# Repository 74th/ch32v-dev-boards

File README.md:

# CH32V Development Board

- [74th. CH32V203C8T6 ProMicro](./ch32v203-promicro/)
- [74th. CH32V003F6P6 ProMicro](./ch32v003-promicro/)
- [74th. CH32X035G8U6 ProMicro for USB PD](./ch32x035-promicro-usb-pd/)
- [74th. CH32X035G8U6 ProMicro for USB Device](./ch32x035-promicro-usb-device/)
- [74th. CH32V00xJxM6 SOIC-8 Dev Board](./ch32v00x-soic8/)
- [74th. CH32V006K8U6 Full Dev Board](./ch32v006-full/)

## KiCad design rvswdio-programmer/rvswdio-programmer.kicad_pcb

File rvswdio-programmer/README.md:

# RVSWDIO Programmer

- Semantics [kicanvas](https://kicanvas.org/?github=https%3A%2F%2Fgithub.com%2F74th%2Fch32v-dev-boards%2Fblob%2Frvswdio-programmer%2F1.0.1%2Frvswdio-programmer%2Frvswdio-programmer.kicad_sch)
- PCB [kicanvas](https://kicanvas.org/?github=https%3A%2F%2Fgithub.com%2F74th%2Fch32v-dev-boards%2Fblob%2Frvswdio-programmer%2F1.0.1%2Frvswdio-programmer%2Frvswdio-programmer.kicad_pcb)

firmware

https://github.com/cnlohr/rv003usb/tree/master/rvswdio_programmer

The on/off levels of the power switch pin need to be swapped.

```h
#define POWER_ON 0
#define POWER_OFF 1
```

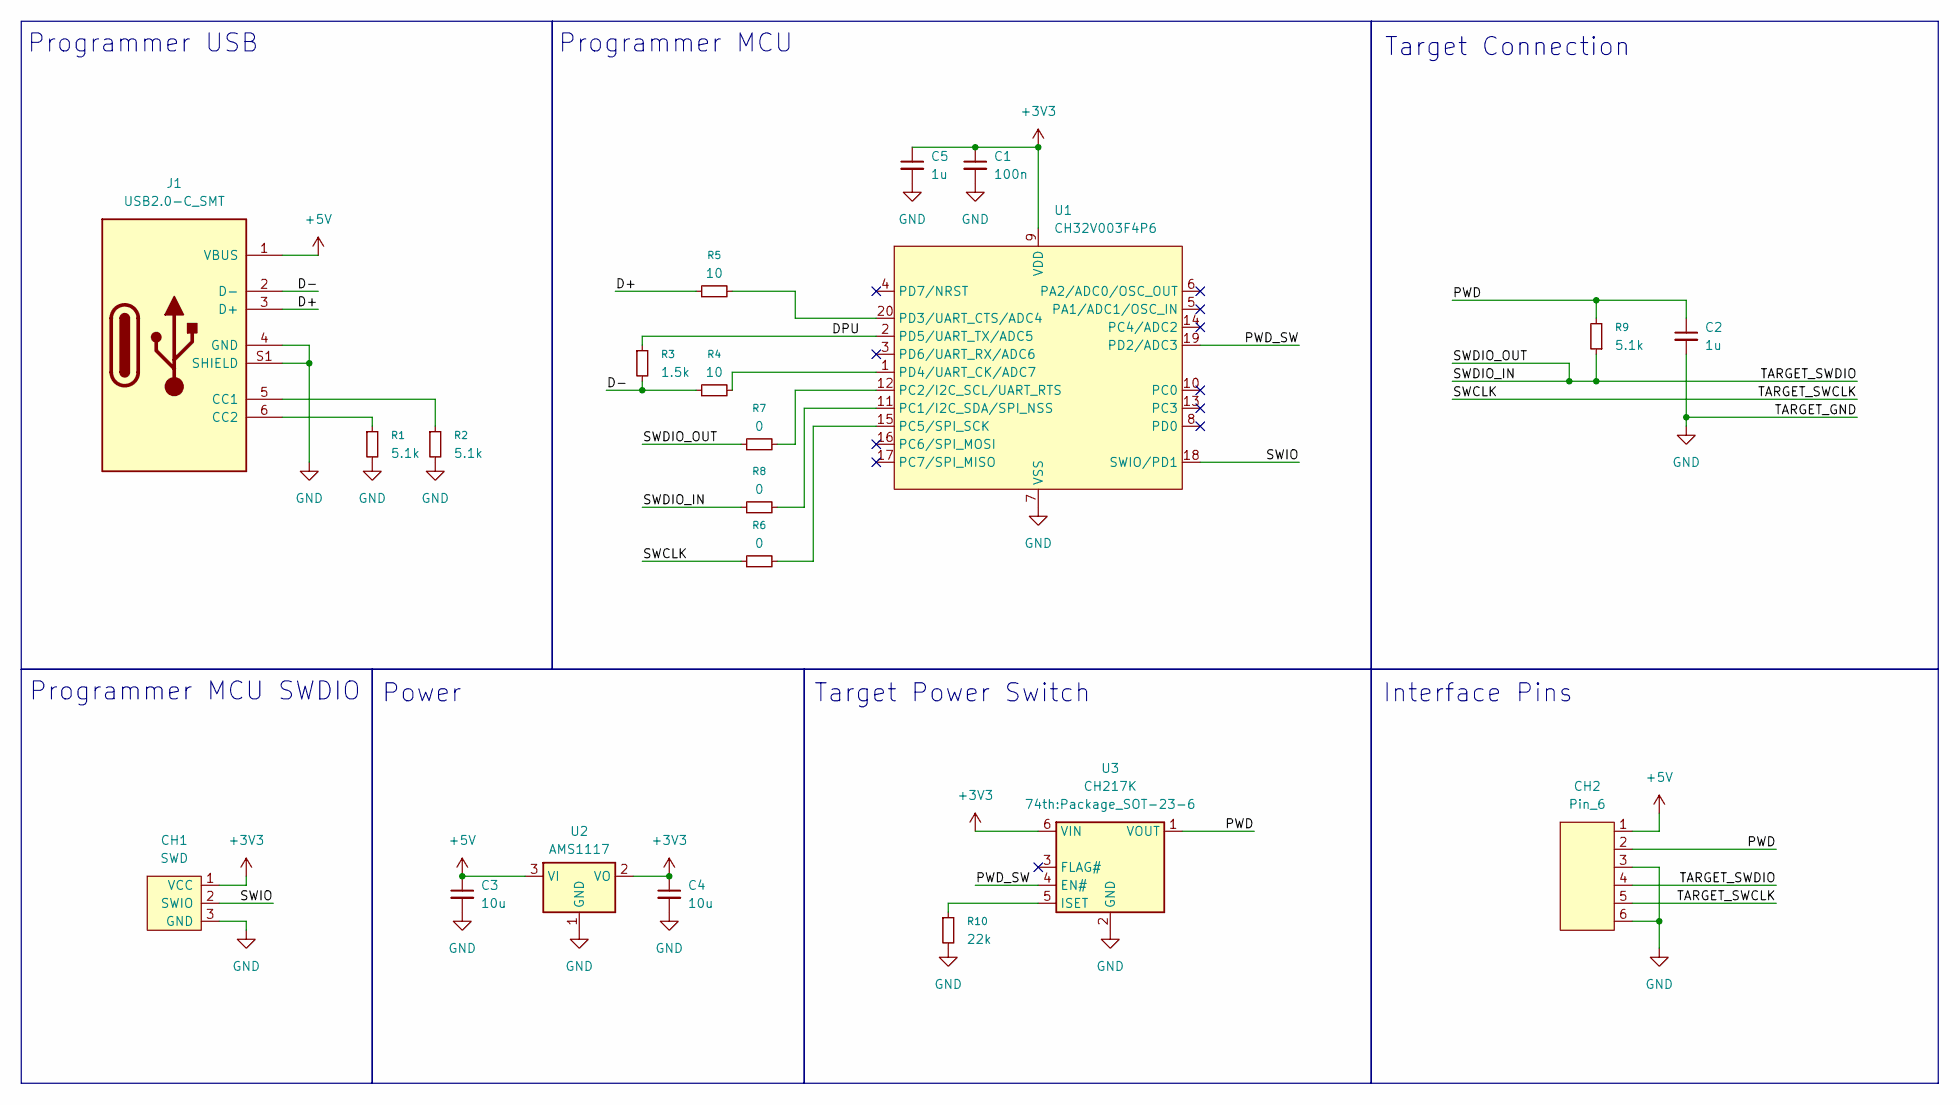
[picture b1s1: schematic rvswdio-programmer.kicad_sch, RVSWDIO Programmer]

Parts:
C1: 100n; Capacitor_0603_1608
C2, C5: 1u; Capacitor_0603_1608
C3, C4: 10u; Capacitor_0603_1608
CH1: SWD; PinOut_Pin_3_3GND
CH2: Pin_6; PinOut_Pin_6_GND
J1: USB2.0-C_SMT; Connector_USB-C-Receptacle_SMT_12-Pin_Simple
R1, R2, R9: 5.1k; Register_0603_1608
R3: 1.5k; Register_0603_1608
R4, R5: 10; Register_0603_1608
R6, R7, R8: 0; Register_0603_1608
R10: 22k; Register_0603_1608
U1: CH32V003F4P6; Package_TSSOP-20_4.4x6.5mm_P0.65mm
U2: AMS1117; Package_SOT-89-3
U3: CH217K; Package_SOT-23-6

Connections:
+3V3: C1.1, C4.1, C5.1, CH1.1 (VCC), U1.9 (VDD), U2.2 (VO), U3.6 (VIN)
+5V: C3.1, CH2.1, J1.1 (VBUS), U2.3 (VI)
/D+: J1.3 (D+), R5.1
/D-: J1.2 (D-), R3.2, R4.1
/DPU: R3.1, U1.2 (PD5/UART_TX/ADC5)
/PWD: C2.1, CH2.2, R9.2, U3.1 (VOUT)
/PWD_SW: U1.19 (PD2/ADC3), U3.4 (EN#)
/SWCLK: CH2.5, R6.1
/SWDIO_IN: CH2.4, R7.1, R8.1, R9.1
/SWIO: CH1.2 (SWIO), U1.18 (SWIO/PD1)
GND: C1.2, C2.2, C3.2, C4.2, C5.2, CH1.3 (GND), CH2.3, CH2.6, J1.4 (GND), J1.S1 (SHIELD), R1.2, R2.2, R10.2, U1.7 (VSS), U2.1 (GND), U3.2 (GND)
unnamed: J1.5 (CC1), R2.1
unnamed: J1.6 (CC2), R1.1
unnamed: R8.2, U1.11 (PC1/I2C_SDA/SPI_NSS)
unnamed: R7.2, U1.12 (PC2/I2C_SCL/UART_RTS)
unnamed: R6.2, U1.15 (PC5/SPI_SCK)
unnamed: R5.2, U1.20 (PD3/UART_CTS/ADC4)
unnamed: R4.2, U1.1 (PD4/UART_CK/ADC7)
unnamed: R10.1, U3.5 (ISET)

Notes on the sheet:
Target Connection
Target Power Switch
Interface Pins
Power
Programmer MCU
Programmer USB
Programmer MCU SWDIO

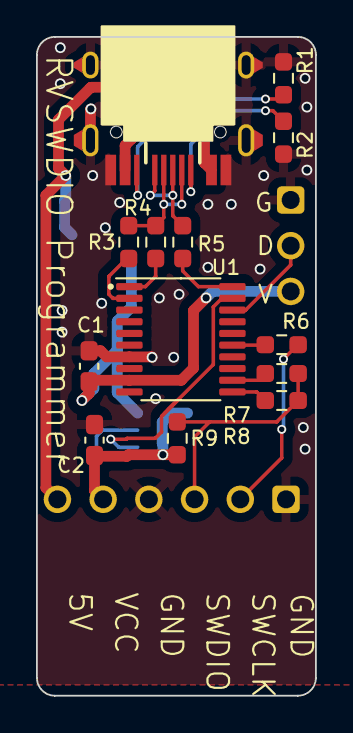
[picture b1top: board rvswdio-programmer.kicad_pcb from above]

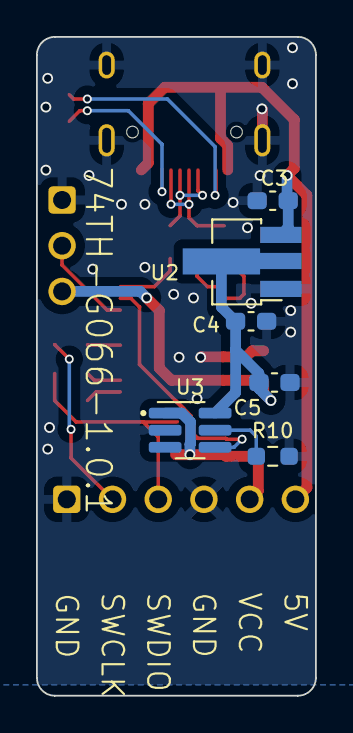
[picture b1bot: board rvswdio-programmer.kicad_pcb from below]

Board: 2 copper layers, 15.5 x 36.6 mm, 21 parts (6 on the bottom side), 19 nets.

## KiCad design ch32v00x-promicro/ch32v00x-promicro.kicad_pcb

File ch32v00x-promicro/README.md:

# WCH CH32V00x ProMicro-Sized Development Board

I forked the CH32V003 ProMicro v1.3.0 to simplify it by removing the USB wiring.

🇯🇵

CH32V003 ProMicro v1.3.0から、USBへの配線を取り除いてシンプルにするために、forkしました。

## features

- ProMicro size
  - To replicate the ProMicro, the CH32V003 lacks sufficient GPIOs, so PC1 is connected to both pin 5 (2/SDA) and pin 13 (10/A10).
- The MCU's VCC is set to 3.3V, but can be switched to 5V by connecting JP1 and removing the U2 3.3V regulator.
- The oscillator used is the MCU's built-in oscillator.

🇯🇵

- ProMicroサイズ
  - ProMicro を再現するには、CH32V003 は GPIO の数が足りないため、PC1が 5ピン（2/SDA）と13ピン（10/A10）に接続されています。
- MCU の VCC は 3.3V になっていますが、JP1 を接続し、U2 3.3V レギュレータを外すことで、5V にすることができます。
- 発振器にはMCU内蔵発振器を使います

## CH32V00x ProMicro v1.3.1

### Changes

- Added SWIO and GND ports for WCH-LinkE connection
- Remove USB Data lines

🇯🇵

- WCH-LinkE接続用にSWIO、GNDポートを追加
- USB データラインを削除

### DataSheet

- Semantics [PDF](docs/ch32v00x-promicro-semantics-v1.3.1.pdf) [kicanvas](https://kicanvas.org/?github=https%3A%2F%2Fgithub.com%2F74th%2Fch32v-dev-boards%2Fblob%2Fch32v00x-promicro%2F1.3.1%2Fch32v00x-promicro%2Fch32v00x-promicro.kicad_sch)
- PCB [kicanvas](https://kicanvas.org/?github=https%3A%2F%2Fgithub.com%2F74th%2Fch32v-dev-boards%2Fblob%2Fch32v00x-promicro%2F1.3.1%2Fch32v00x-promicro%2Fch32v00x-promicro.kicad_pcb)

### Pin Out

### BOM

| Reference | Name                                 | Quantity |
| --------- | ------------------------------------ | -------- |
| C1, C2    | Capacitor 0805 10uF                  | 2        |
| C4        | Capacitor 0805 100nF                 | 1        |
| D1        | LED 0805 Blue                        | 1        |
| J1        | USB Type-C Receptacle                | 1        |
| J2        | Pin Header 2x5 Pitch 1.27mm          | 1        |
| JP1       | Jumper SolderJumper_2_Open           | 1        |
| R3, R4    | Register 0805 5.1kΩ                  | 2        |
| 10        | Register 0805 10kΩ                   | 1        |
| SW1       | Button SKRPABE010                    | 1        |
| U1        | Regulator 3.3V SOT-89 AMS1117-3.3    | 1        |
| U2        | MCU TSSOP20 WCH CH32V003F4P6         | 1        |
| U3        | USB Power Protection IC CH213 SOT-23 | 1        |

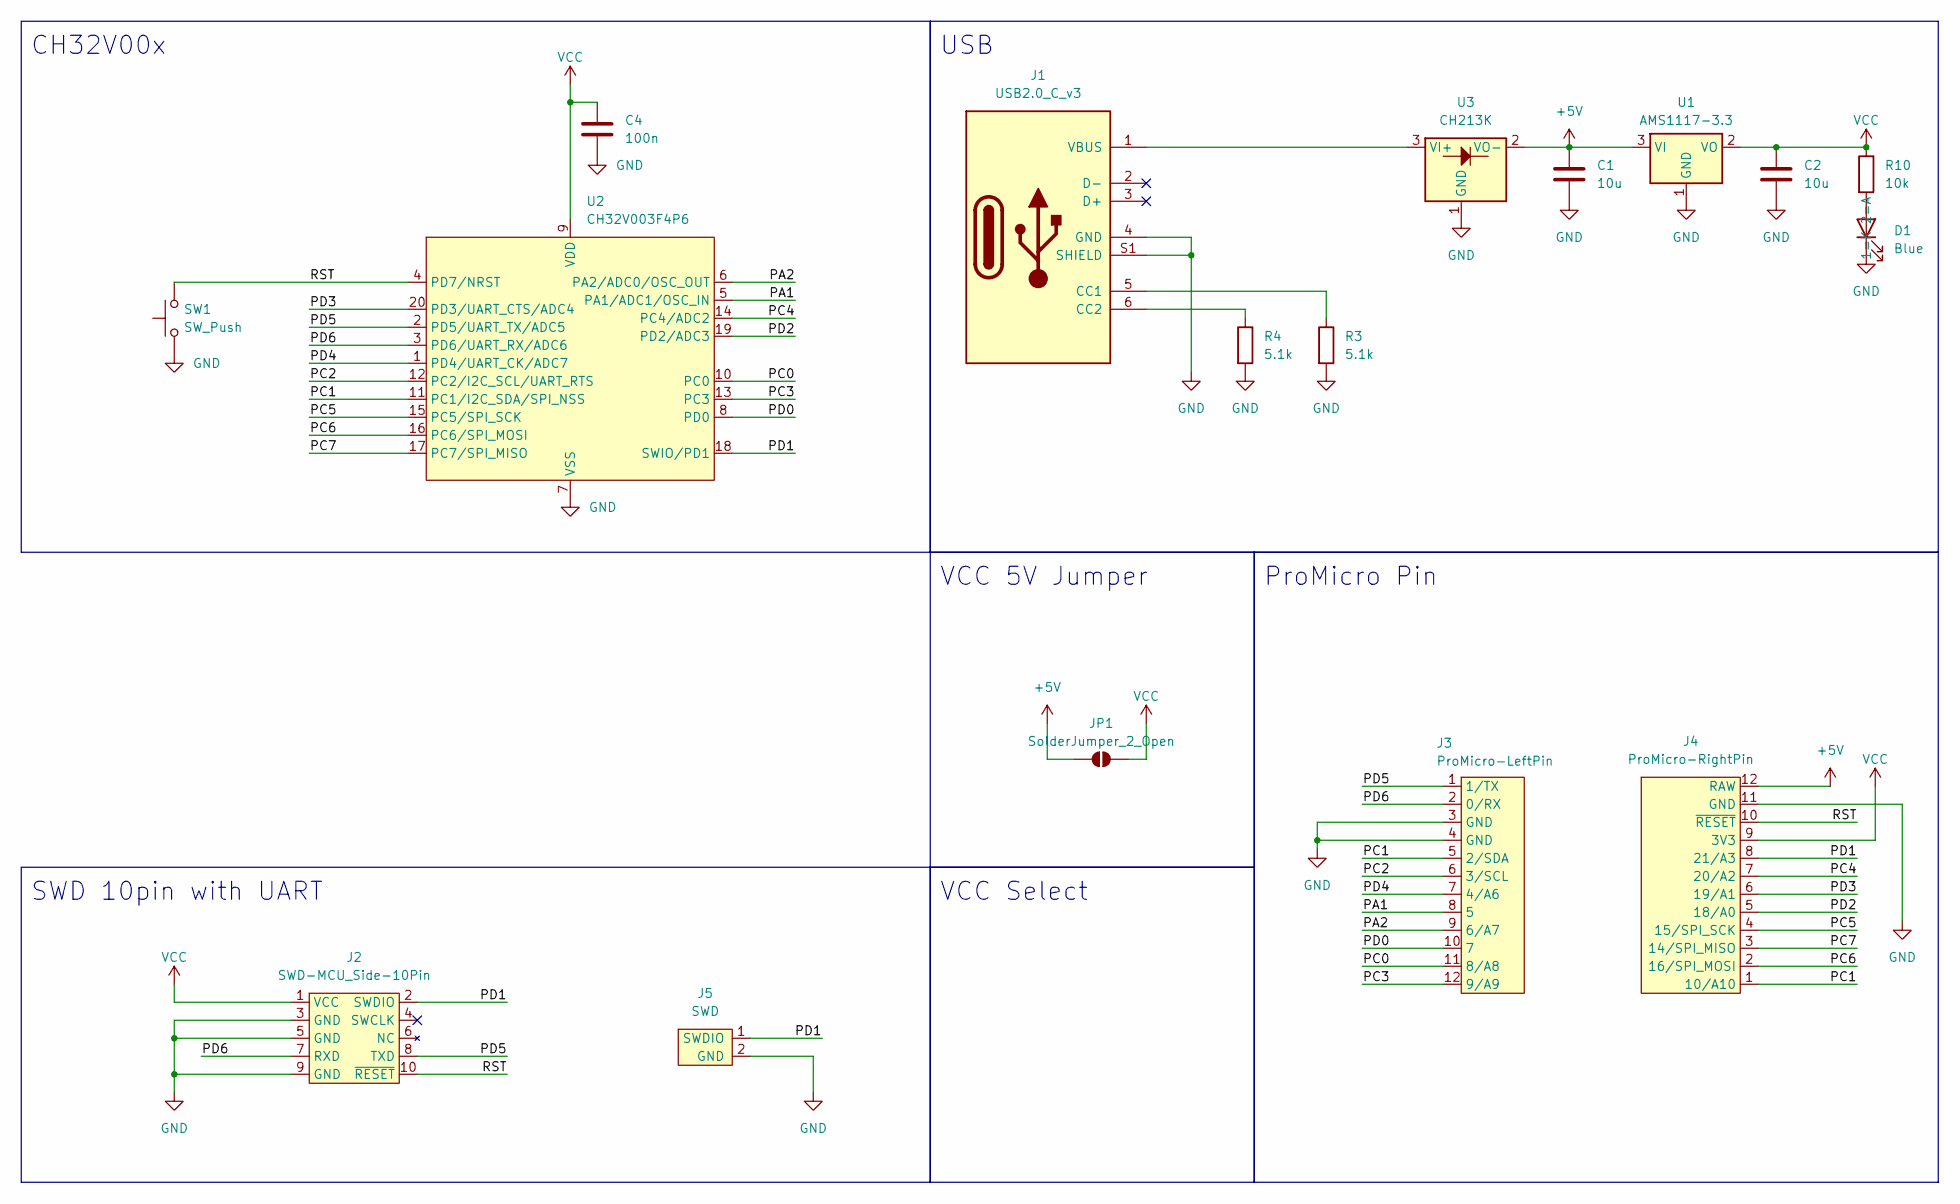
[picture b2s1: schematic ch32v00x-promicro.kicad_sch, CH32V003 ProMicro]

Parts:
C1, C2: 10u; Capacitor_0603_1608
C4: 100n; Capacitor_0603_1608
D1: Blue; LED_0805_2012
J1: USB2.0_C_v3; Connector_USB-C-Receptacle_SMT_12-Pin_Simple
J2: SWD-MCU_Side-10Pin; Connector_HalfPinHeader_SWD
J3: ProMicro-LeftPin; PinOut_ProMicro-LIKE_LEFT
J4: ProMicro-RightPin; PinOut_ProMicro-LIKE_RIGHT
J5: SWD; PinOut_Pin_2_2GND
JP1: SolderJumper_2_Open; SolderJumper-2
R3, R4: 5.1k; Register_0603_1608
R10: 10k; Register_0603_1608
SW1: SW_Push; Switch_SKRPABE010
U1: AMS1117-3.3; Package_SOT-89-3
U2: CH32V003F4P6; Package_TSSOP-20_4.4x6.5mm_P0.65mm
U3: CH213K; Package_SOT-23

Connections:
+5V: C1.1, J4.12 (RAW), JP1.1 (A), U1.3 (VI), U3.2 (VO-)
/PA1: J3.8 (5), U2.5 (PA1/ADC1/OSC_IN)
/PA2: J3.9 (6/A7), U2.6 (PA2/ADC0/OSC_OUT)
/PC0: J3.11 (8/A8), U2.10 (PC0)
/PC1: J3.5 (2/SDA), J4.1 (10/A10), U2.11 (PC1/I2C_SDA/SPI_NSS)
/PC2: J3.6 (3/SCL), U2.12 (PC2/I2C_SCL/UART_RTS)
/PC3: J3.12 (9/A9), U2.13 (PC3)
/PC4: J4.7 (20/A2), U2.14 (PC4/ADC2)
/PC5: J4.4 (15/SPI_SCK), U2.15 (PC5/SPI_SCK)
/PC6: J4.2 (16/SPI_MOSI), U2.16 (PC6/SPI_MOSI)
/PC7: J4.3 (14/SPI_MISO), U2.17 (PC7/SPI_MISO)
/PD0: J3.10 (7), U2.8 (PD0)
/PD1: J2.2 (SWDIO), J4.8 (21/A3), J5.1 (SWDIO), U2.18 (SWIO/PD1)
/PD2: J4.5 (18/A0), U2.19 (PD2/ADC3)
/PD3: J4.6 (19/A1), U2.20 (PD3/UART_CTS/ADC4)
/PD4: J3.7 (4/A6), U2.1 (PD4/UART_CK/ADC7)
/PD5: J2.8 (TXD), J3.1 (1/TX), U2.2 (PD5/UART_TX/ADC5)
/PD6: J2.7 (RXD), J3.2 (0/RX), U2.3 (PD6/UART_RX/ADC6)
/RST: J2.10 (~RESET), J4.10 (~RESET), SW1.2, U2.4 (PD7/NRST)
GND: C1.2, C2.2, C4.2, D1.1 (K), J1.4 (GND), J1.S1 (SHIELD), J2.3 (GND), J2.5 (GND), J2.9 (GND), J3.3 (GND), J3.4 (GND), J4.11 (GND), J5.2 (GND), R3.2, R4.2, SW1.1, U1.1 (GND), U2.7 (VSS), U3.1 (GND)
unnamed: D1.2 (A), R10.2
unnamed: J1.5 (CC1), R3.1
unnamed: J1.6 (CC2), R4.1
unnamed: J1.1 (VBUS), U3.3 (VI+)
VCC: C2.1, C4.1, J2.1 (VCC), J4.9 (3V3), JP1.2 (B), R10.1, U1.2 (VO), U2.9 (VDD)

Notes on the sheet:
VCC 5V Jumper
CH32V00x
VCC Select
ProMicro Pin
USB
SWD 10pin with UART

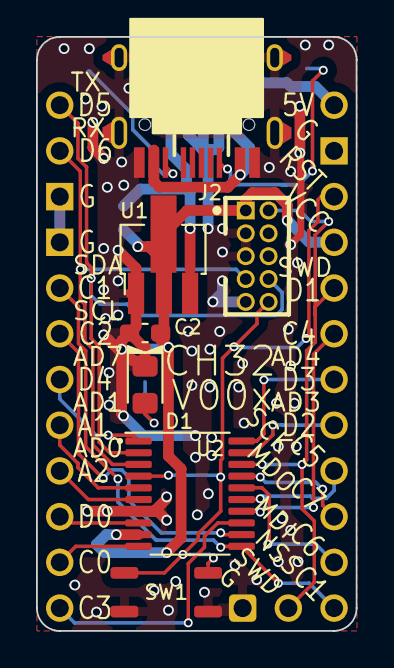
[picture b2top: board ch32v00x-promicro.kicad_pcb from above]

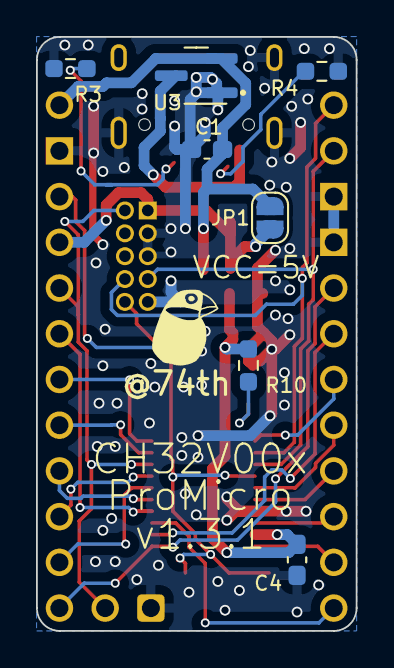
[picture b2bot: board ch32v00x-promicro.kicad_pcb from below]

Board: 2 copper layers, 17.8 x 33.0 mm, 19 parts (9 on the bottom side), 25 nets.

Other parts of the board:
MISC-ACCOUNTTEXT: 74th-text
MISC-ACCOUNTTEXT#2: 74th-text

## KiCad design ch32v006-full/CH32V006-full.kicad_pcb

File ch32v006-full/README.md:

# CH32V006-full Dev Board

## target mcu

- CH32V006K8U6

## 1.0.0

### PinOut

### BOM

| Reference | Name                            | Package          | Quantity |
| --------- | ------------------------------- | ---------------- | -------- |
| C1-2      | Capacitor 10uF                  | SMD 0603in 1608M | 2        |
| C3-4      | Capacitor 100nF                 | SMD 0603in 1608M | 2        |
| J1        | USB Type-C Receptacle           |                  | 1        |
| J2        | Box Pin Header 2x5 Pitch 1.27mm | TH               | 1        |
| JP1       | Jumper Jumper_2_Open            |                  | 1        |
| R1-2      | Register 5.1kΩ                  | SMD 0603in 1608M | 2        |
| R3-4      | Register 10Ω (NC)               | SMD 0603in 1608M | 2        |
| R5        | Register 1.5kΩ (NC)             | SMD 0603in 1608M | 1        |
| SW1       | Button SKRPABE010               |                  | 1        |
| U1        | MCU WCH CH32V006K8U6            | QFN32            | 1        |
| U2        | USB Power Protection IC CH213K  | SOT-23           | 1        |
| U3        | Regulator 3.3V AMS1117-3.3      | SOT-89           | 1        |

### DataSheet

- Semantics [PDF](docs/CH32V006-full-1.0.0-semantics.pdf) [kicanvas](https://kicanvas.org/?github=https%3A%2F%2Fgithub.com%2F74th%2Fch32v-dev-boards%2Fblob%2Fch32v006-full%2F1.0.0%2Fch32v006-full%2FCH32V006-full.kicad_sch)
- PCB [kicanvas](https://kicanvas.org/?github=https%3A%2F%2Fgithub.com%2F74th%2Fch32v-dev-boards%2Fblob%2Fch32v006-full%2F1.0.0%2Fch32v006-full%2FCH32V006-full.kicad_pcb)

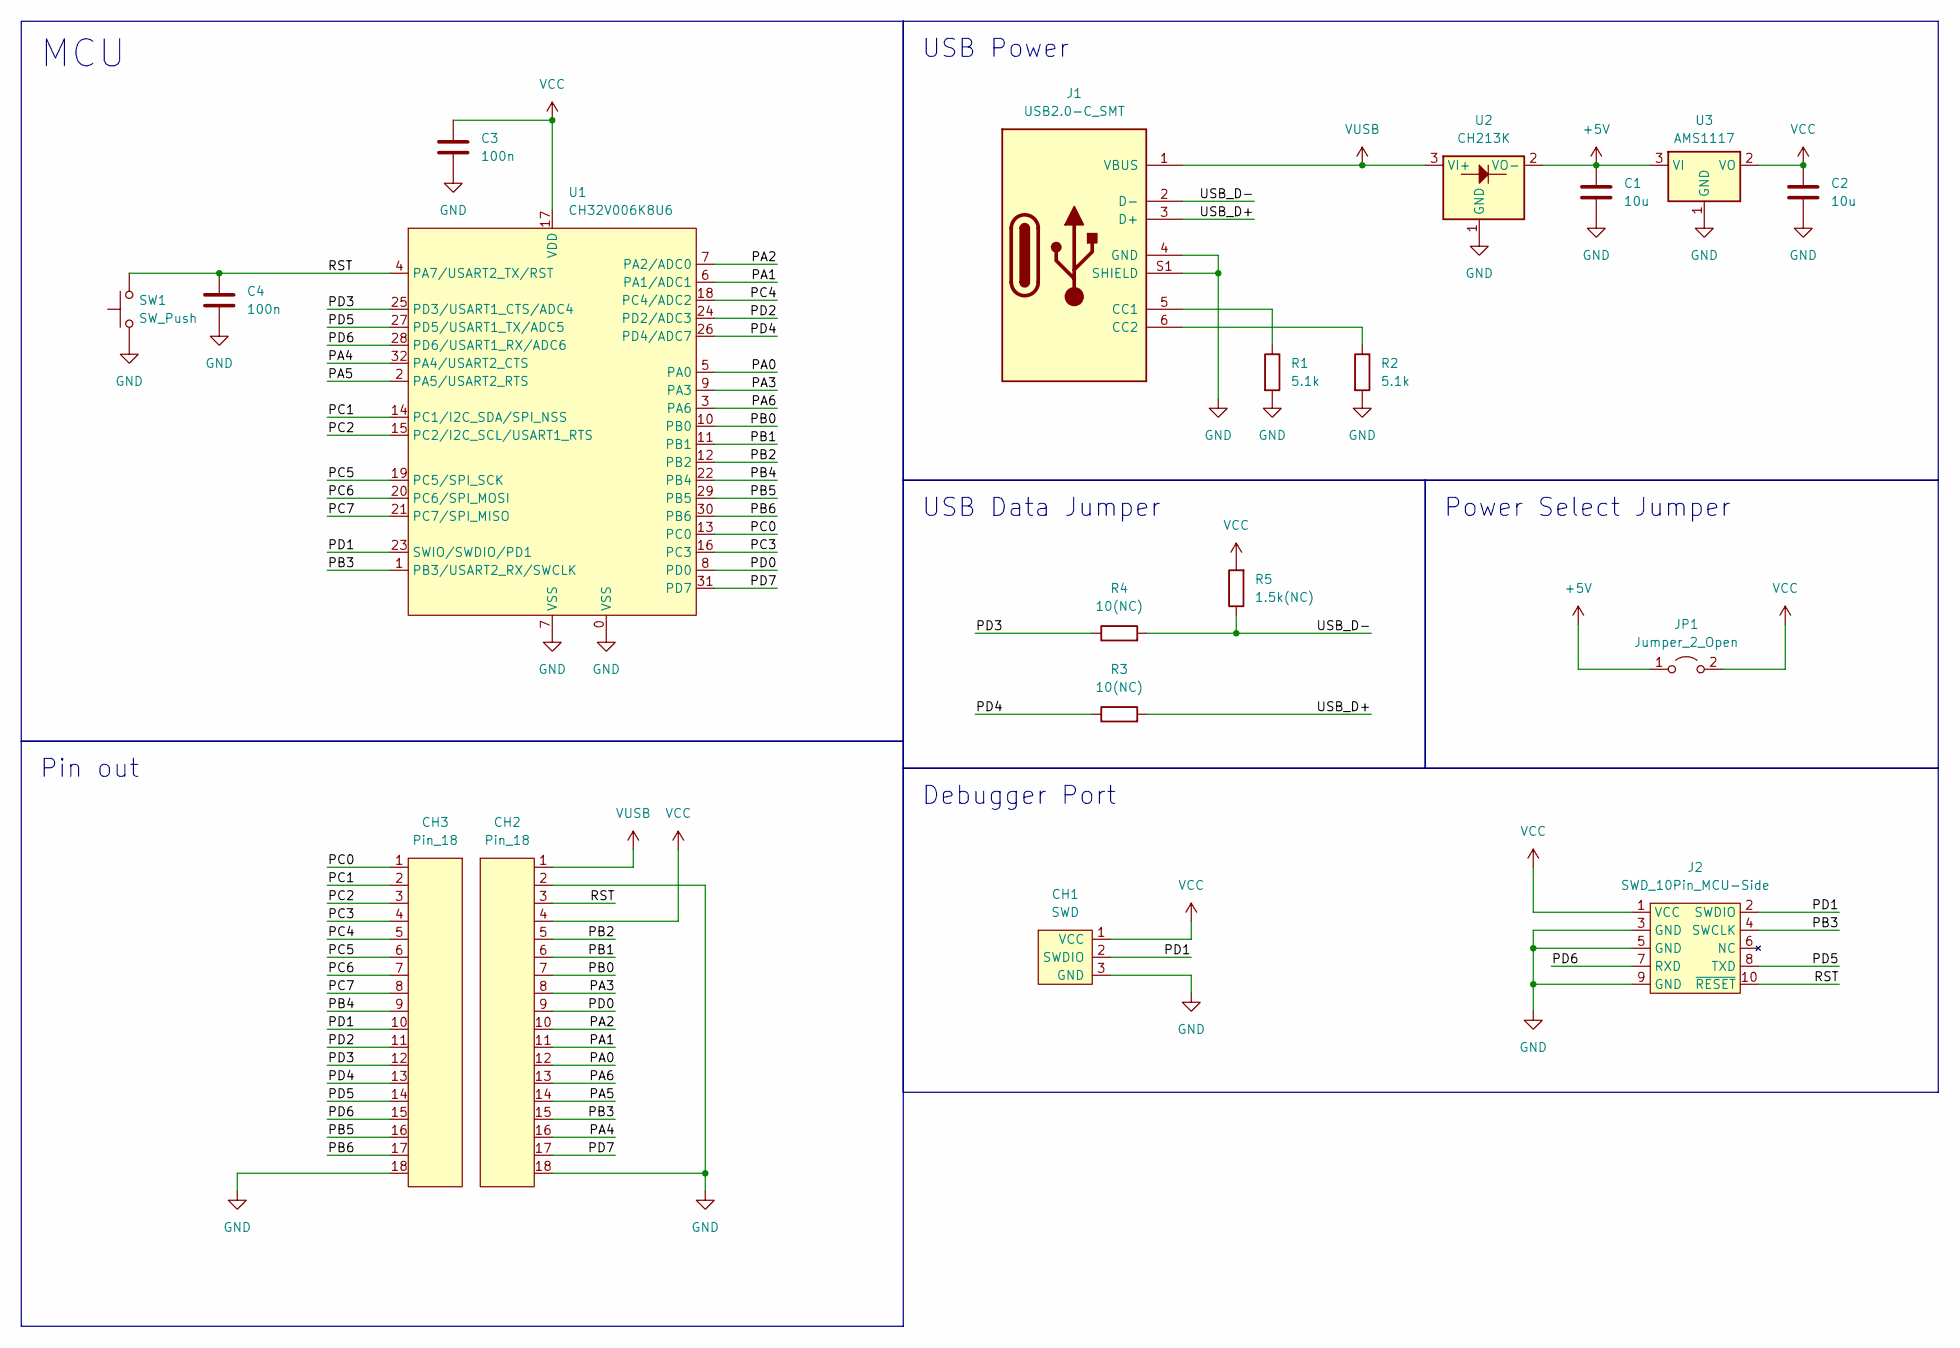
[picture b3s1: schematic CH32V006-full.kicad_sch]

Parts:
C1, C2: 10u; Capacitor_0603_1608
C3, C4: 100n; Capacitor_0603_1608
CH1: SWD; PinOut_Pin_3_3GND
CH2, CH3: Pin_18; PinOut_Pin_18
J1: USB2.0-C_SMT; Connector_USB-C-Receptacle_SMT_12-Pin_Simple
J2: SWD_10Pin_MCU-Side; Connector_HalfPinHeader_SWD
JP1: Jumper_2_Open; SolderJumper-2
R1, R2: 5.1k; Register_0603_1608
R3, R4: 10(NC); Register_0603_1608
R5: 1.5k(NC); Register_0603_1608
SW1: SW_Push; Switch_SKRPABE010
U1: CH32V006K8U6; Package_QFN-32-1EP_4x4mm_P0.4mm_EP2.7x2.7mm_hand
U2: CH213K; Package_SOT-23
U3: AMS1117; Package_SOT-89-3

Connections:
+5V: C1.1, JP1.1 (A), U2.2 (VO-), U3.3 (VI)
/PA0: CH2.12, U1.5 (PA0)
/PA1: CH2.11, U1.6 (PA1/ADC1)
/PA3: CH2.8, U1.9 (PA3)
/PA4: CH2.16, U1.32 (PA4/USART2_CTS)
/PA5: CH2.14, U1.2 (PA5/USART2_RTS)
/PA6: CH2.13, U1.3 (PA6)
/PB0: CH2.7, U1.10 (PB0)
/PB1: CH2.6, U1.11 (PB1)
/PB2: CH2.5, U1.12 (PB2)
/PB3: CH2.15, J2.4 (SWCLK), U1.1 (PB3/USART2_RX/SWCLK)
/PB4: CH3.9, U1.22 (PB4)
/PB5: CH3.16, U1.29 (PB5)
/PB6: CH3.17, U1.30 (PB6)
/PC0: CH3.1, U1.13 (PC0)
/PC1: CH3.2, U1.14 (PC1/I2C_SDA/SPI_NSS)
/PC2: CH3.3, U1.15 (PC2/I2C_SCL/USART1_RTS)
/PC3: CH3.4, U1.16 (PC3)
/PC4: CH3.5, U1.18 (PC4/ADC2)
/PC5: CH3.6, U1.19 (PC5/SPI_SCK)
/PC6: CH3.7, U1.20 (PC6/SPI_MOSI)
/PC7: CH3.8, U1.21 (PC7/SPI_MISO)
/PD0: CH2.9, U1.8 (PD0)
/PD1: CH1.2 (SWDIO), CH3.10, J2.2 (SWDIO), U1.23 (SWIO/SWDIO/PD1)
/PD2: CH3.11, U1.24 (PD2/ADC3)
/PD3: CH3.12, R4.1, U1.25 (PD3/USART1_CTS/ADC4)
/PD4: CH3.13, R3.1, U1.26 (PD4/ADC7)
/PD5: CH3.14, J2.8 (TXD), U1.27 (PD5/USART1_TX/ADC5)
/PD6: CH3.15, J2.7 (RXD), U1.28 (PD6/USART1_RX/ADC6)
/PD7: CH2.17, U1.31 (PD7)
/RST: C4.1, CH2.3, J2.10 (~RESET), SW1.2, U1.4 (PA7/USART2_TX/RST)
/USB_D+: J1.3 (D+), R3.2
/USB_D-: J1.2 (D-), R4.2, R5.1
unnamed: J1.5 (CC1), R1.1
unnamed: J1.6 (CC2), R2.1
VCC: C2.1, C3.1, CH1.1 (VCC), CH2.4, J2.1 (VCC), JP1.2 (B), R5.2, U1.17 (VDD), U3.2 (VO)
VUSB: CH2.1, J1.1 (VBUS), U2.3 (VI+)

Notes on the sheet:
USB Data Jumper
Power Select Jumper
Debugger Port
MCU
USB Power
Pin out

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
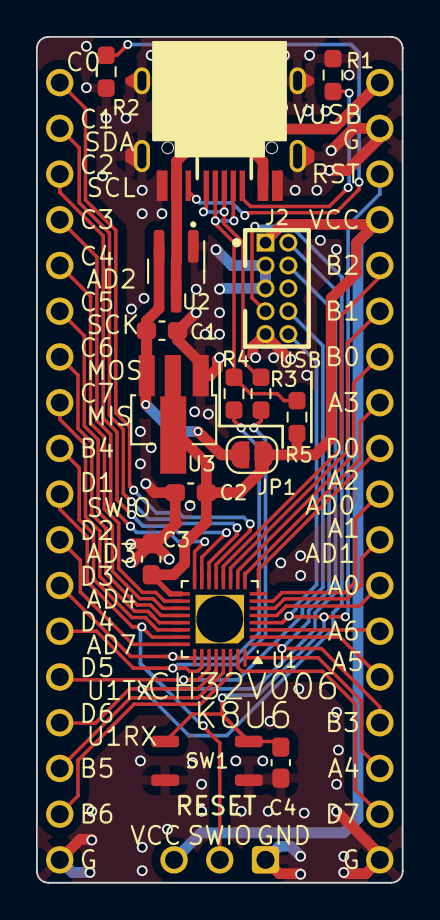
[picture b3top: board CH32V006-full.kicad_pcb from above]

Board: 2 copper layers, 20.3 x 47.0 mm, 20 parts (1 on the bottom side), 39 nets.

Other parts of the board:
MISC-ICON: LOGO; Logo_74th_5mm

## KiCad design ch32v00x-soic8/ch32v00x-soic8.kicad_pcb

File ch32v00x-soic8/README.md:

# CH32V00xJxM6 Dev Board

## target mcu

- CH32V003J4M6
- CH32V002J4M6

## 1.0.0

### PinOut

### BOM

| Reference | Name                           | Package          | Quantity |
| --------- | ------------------------------ | ---------------- | -------- |
| C1-2      | Capacitor 10uF                 | SMD 0603in 1608M | 2        |
| C3        | Capacitor 100nF                | SMD 0603in 1608M | 1        |
| J1        | USB Type-C Receptacle          |                  | 1        |
| JP2       | Jumper Jumper_2_Open           |                  | 1        |
| R1-2      | Register 5.1kΩ                 | SMD 0603in 1608M | 2        |
| U1        | MCU WCH CH32V002J4M6           | SOIC-8           | 1        |
| U2        | USB Power Protection IC CH213K | SOT-23           | 1        |
| U3        | Regulator 3.3V AMS1117-3.3     | SOT-89           | 1        |

### DataSheet

- Semantics [PDF](docs/ch32v00x-soic8-1.0.0-semantics.pdf) [kicanvas](https://kicanvas.org/?github=https%3A%2F%2Fgithub.com%2F74th%2Fch32v-dev-boards%2Fblob%2Fch32v00x-soic8%2F1.0.0%2Fch32v00x-soic8%2Fch32v00x-soic8.kicad_sch)
- PCB [kicanvas](https://kicanvas.org/?github=https%3A%2F%2Fgithub.com%2F74th%2Fch32v-dev-boards%2Fblob%2Fch32v00x-soic8%2F1.0.0%2Fch32v00x-soic8%2Fch32v00x-soic8.kicad_pcb)

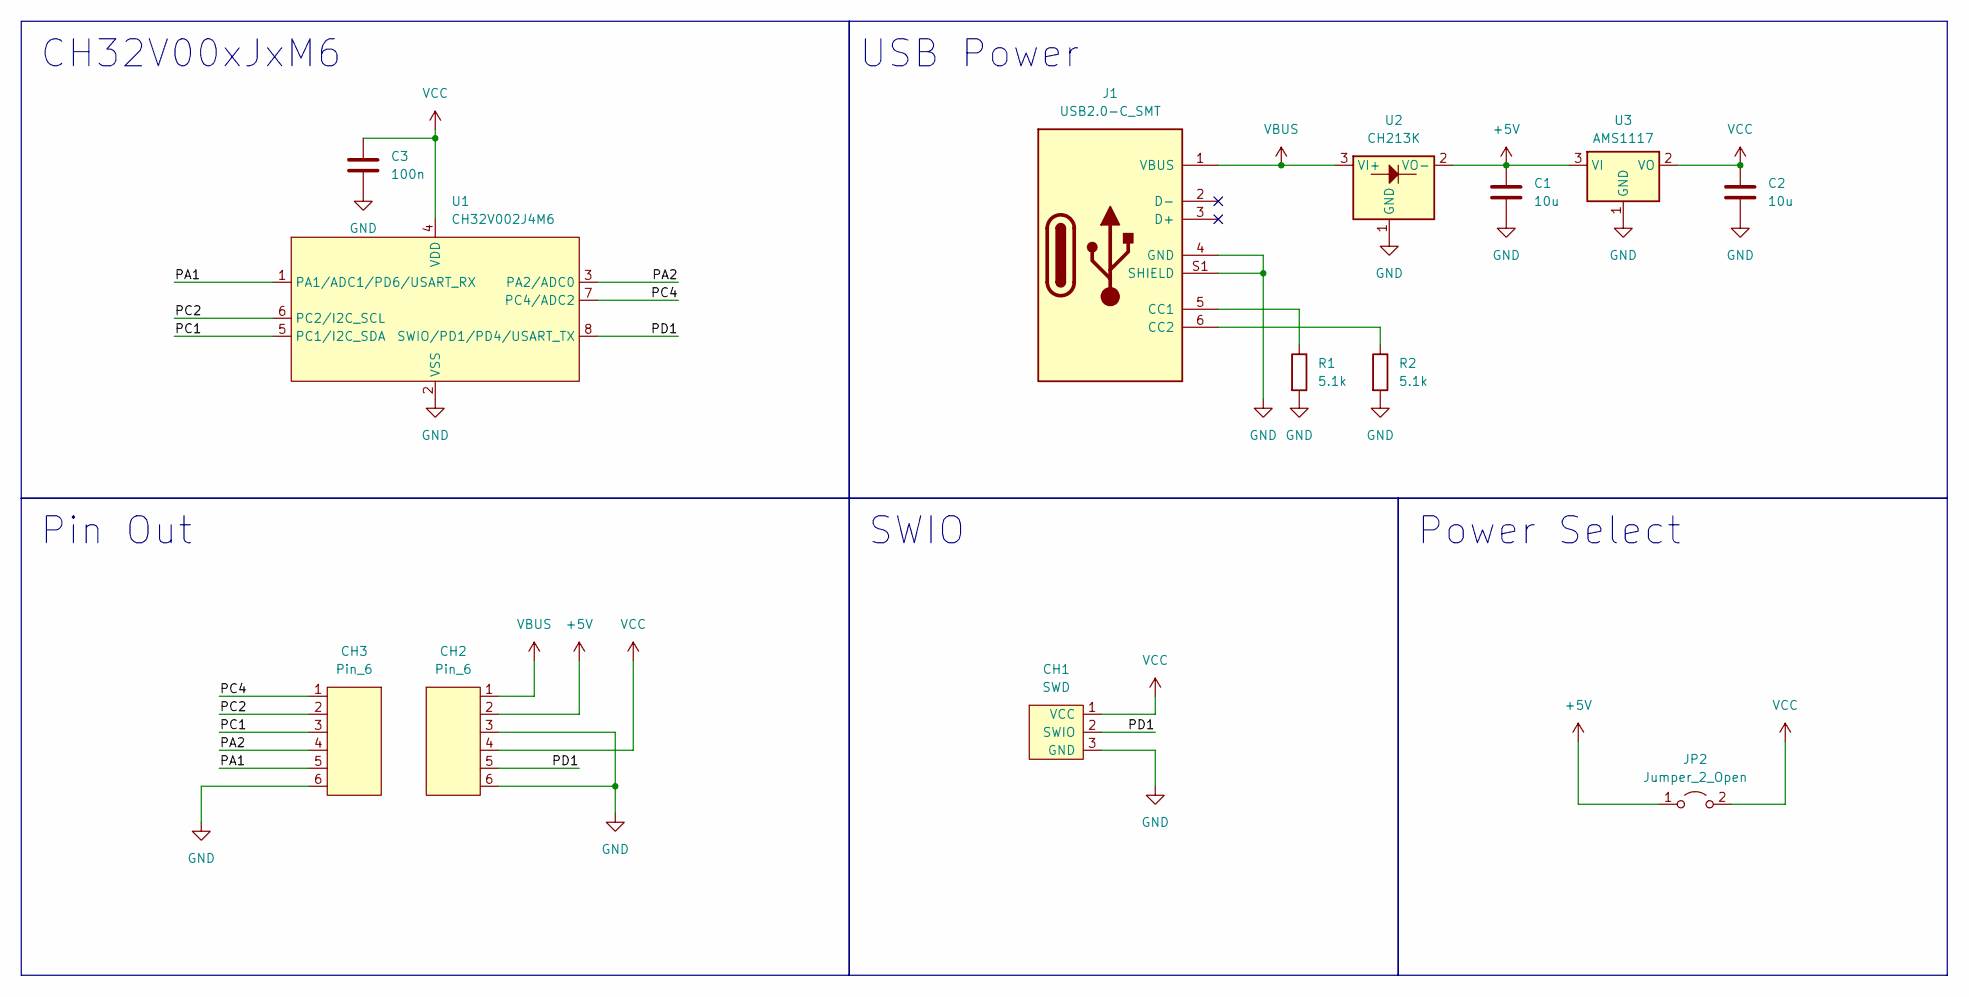
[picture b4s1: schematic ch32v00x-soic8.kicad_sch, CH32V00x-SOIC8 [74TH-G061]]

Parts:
C1, C2: 10u; Capacitor_0603_1608
C3: 100n; Capacitor_0603_1608
CH1: SWD; PinOut_Pin_3_3GND
CH2, CH3: Pin_6; PinOut_Pin_6_GND
J1: USB2.0-C_SMT; Connector_USB-C-Receptacle_SMT_12-Pin_Simple
JP2: Jumper_2_Open; SolderJumper-2
R1, R2: 5.1k; Register_0603_1608
U1: CH32V002J4M6; Package_SOIC-8_3.9x4.9mm_P1.27mm
U2: CH213K; Package_SOT-23
U3: AMS1117; Package_SOT-89-3

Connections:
+5V: C1.1, CH2.2, JP2.1 (A), U2.2 (VO-), U3.3 (VI)
/PA1: CH3.5, U1.1 (PA1/ADC1/PD6/USART_RX)
/PA2: CH3.4, U1.3 (PA2/ADC0)
/PC1: CH3.3, U1.5 (PC1/I2C_SDA)
/PC2: CH3.2, U1.6 (PC2/I2C_SCL)
/PC4: CH3.1, U1.7 (PC4/ADC2)
/PD1: CH1.2 (SWDIO), CH2.5, U1.8 (SWIO/PD1/PD4/USART_TX)
GND: C1.2, C2.2, C3.2, CH1.3 (GND), CH2.3, CH2.6, CH3.6, J1.4 (GND), J1.S1 (SHIELD), R1.2, R2.2, U1.2 (VSS), U2.1 (GND), U3.1 (GND)
unnamed: J1.5 (CC1), R1.1
unnamed: J1.6 (CC2), R2.1
VBUS: CH2.1, J1.1 (VBUS), U2.3 (VI+)
VCC: C2.1, C3.1, CH1.1 (VCC), CH2.4, JP2.2 (B), U1.4 (VDD), U3.2 (VO)

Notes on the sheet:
USB Power
SWIO
Power Select
CH32V00xJxM6
Pin Out

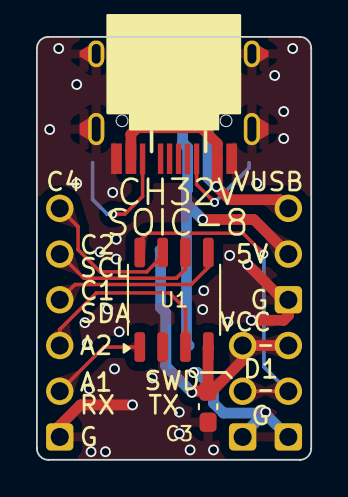
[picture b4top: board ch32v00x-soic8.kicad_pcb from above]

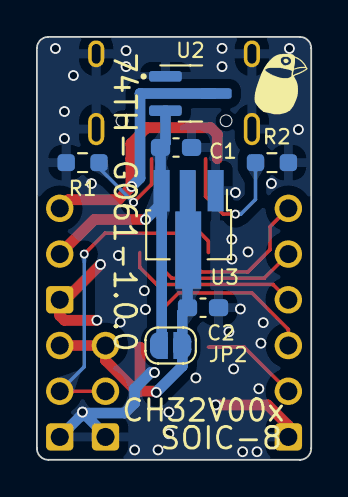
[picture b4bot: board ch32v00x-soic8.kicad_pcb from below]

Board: 2 copper layers, 15.2 x 23.5 mm, 14 parts (8 on the bottom side), 12 nets.

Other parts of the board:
MISC-ICON: LOGO; Logo_74th_4mm
